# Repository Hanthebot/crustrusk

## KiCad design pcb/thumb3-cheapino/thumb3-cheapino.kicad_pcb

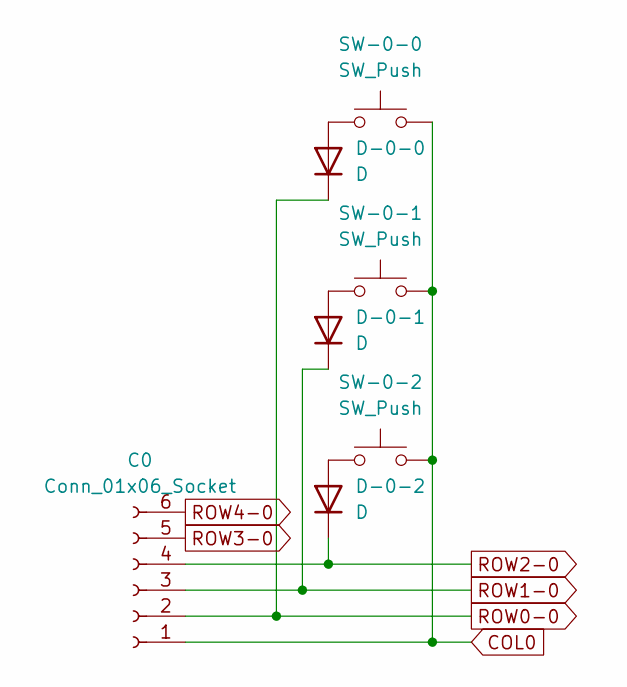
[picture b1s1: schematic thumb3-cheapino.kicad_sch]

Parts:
C0: Conn_01x06_Socket; reversible JST_PH_S6B-PH-K_1x06_P2.00mm_Horizontal
D-0-0, D-0-1, D-0-2: D; Diode_TH_SMD_REVERSIBLE
SW-0-0, SW-0-1, SW-0-2: SW_Push; Kailh_hotswap_only_socket_MX_optional_reversible-MIRROR

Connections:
COL0: C0.1, SW-0-0.2, SW-0-1.2, SW-0-2.2
unnamed: D-0-0.2 (A), SW-0-0.1
unnamed: D-0-1.2 (A), SW-0-1.1
unnamed: D-0-2.2 (A), SW-0-2.1
ROW0-0: C0.2, D-0-0.1 (K)
ROW1-0: C0.3, D-0-1.1 (K)
ROW2-0: C0.4, D-0-2.1 (K)
ROW3-0: C0.5
ROW4-0: C0.6

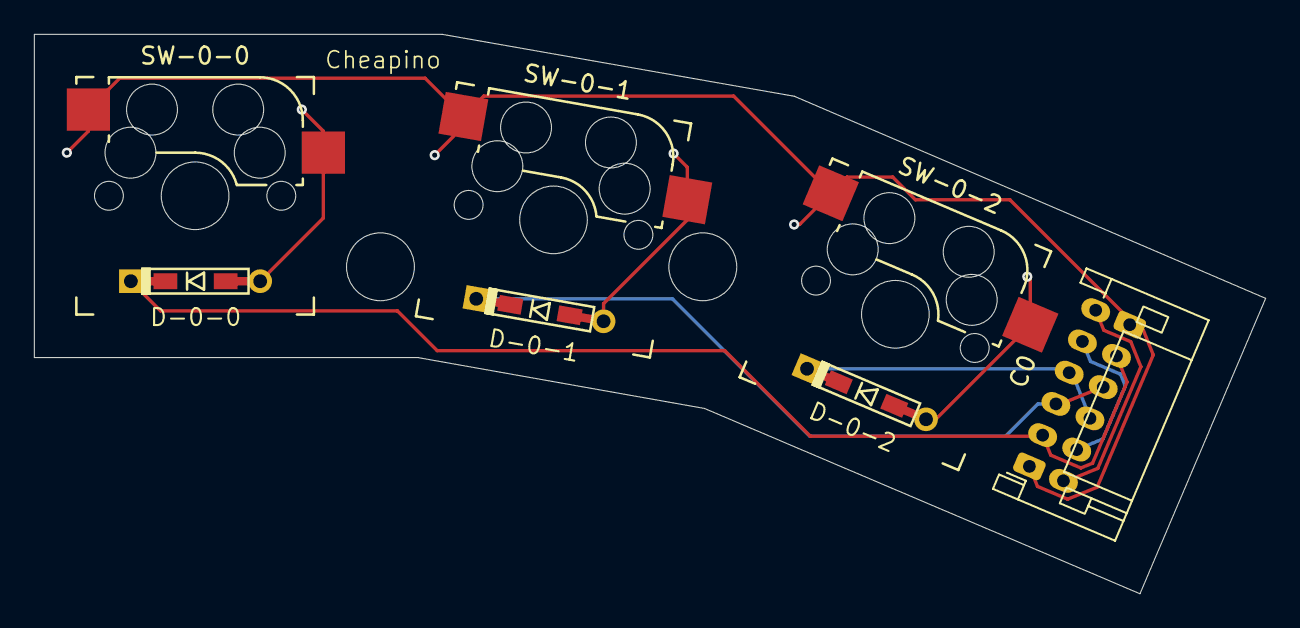
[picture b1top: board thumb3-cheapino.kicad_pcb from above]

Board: 2 copper layers, 72.6 x 33.0 mm, 7 parts (0 on the bottom side), 7 nets.
